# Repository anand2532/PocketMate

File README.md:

# PocketMate
A personal AI companion built on the Raspberry Pi CM5 (4GB; CM4 alternate). PocketMate helps you capture anything important, find it when you need it, and get the next step done: dependable, fast, privacy-conscious, and not a phone replacement.

MVP: push-to-talk voice assistant, local voice/typed notes, searchable memory with source-linked answers, camera OCR, reminders and action items, configurable local/cloud processing, and a physical mic mute. Hardware: 4.3" touchscreen, autofocus camera, dual MEMS mics, battery with USB-C charging, custom carrier PCB and a compact, serviceable enclosure (~125x75x20mm).

See [docs/PRD.md](docs/PRD.md) for the full product brief.

## Repository layout
- `hardware/kicad/` – schematics and carrier PCB (KiCad)
- `mechanical/freecad/` – enclosure CAD (FreeCAD)
- `software/` – Linux services, Qt/QML UI, firmware
- `docs/` – PRD and project documentation
- `research/` – notes, datasheets, experiments

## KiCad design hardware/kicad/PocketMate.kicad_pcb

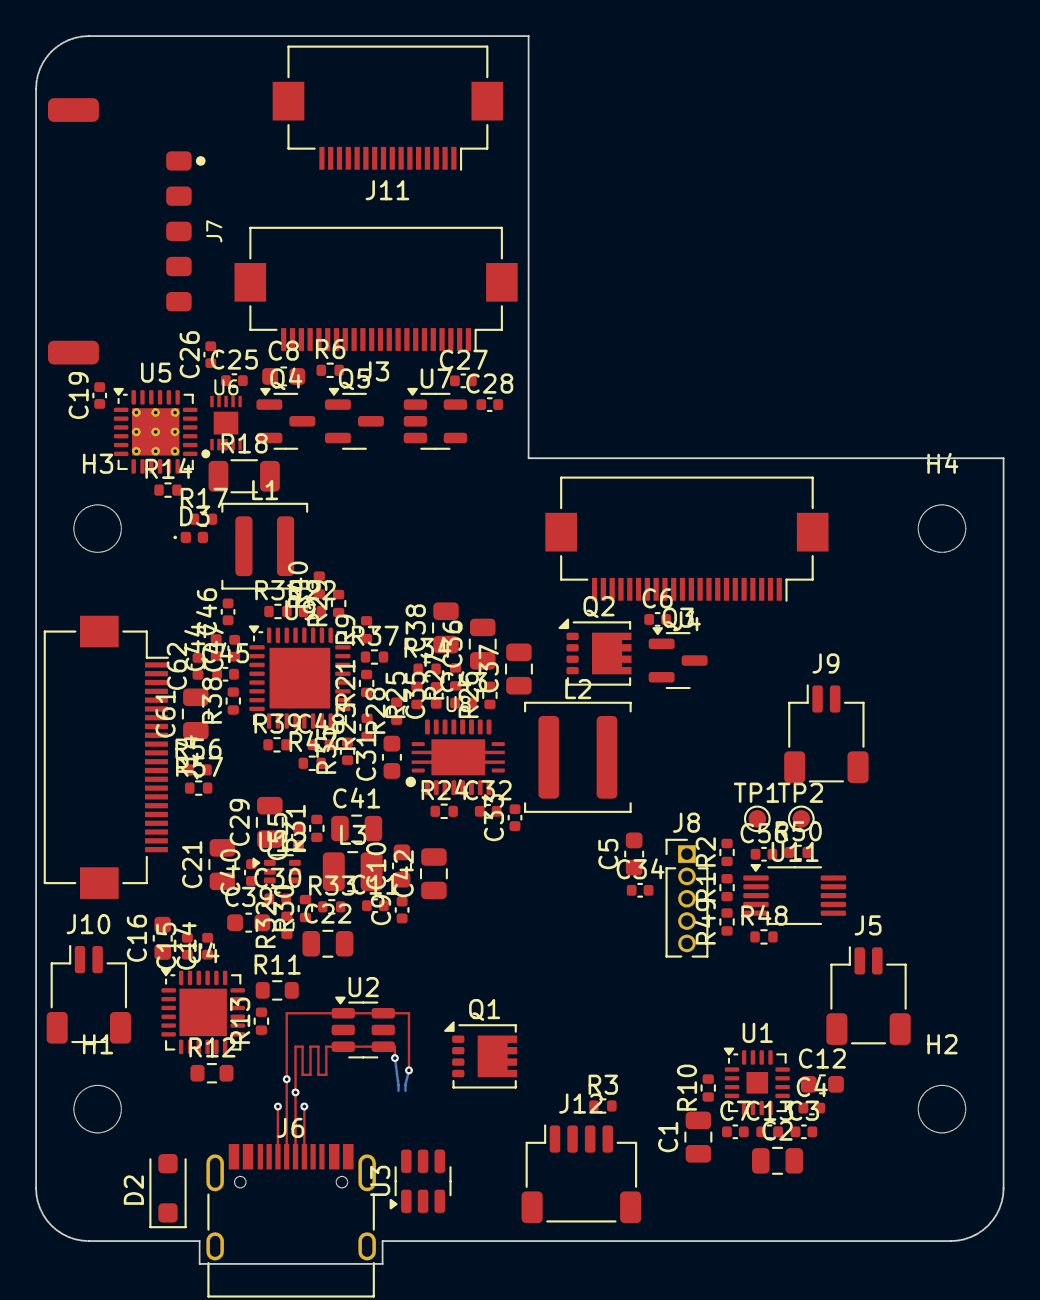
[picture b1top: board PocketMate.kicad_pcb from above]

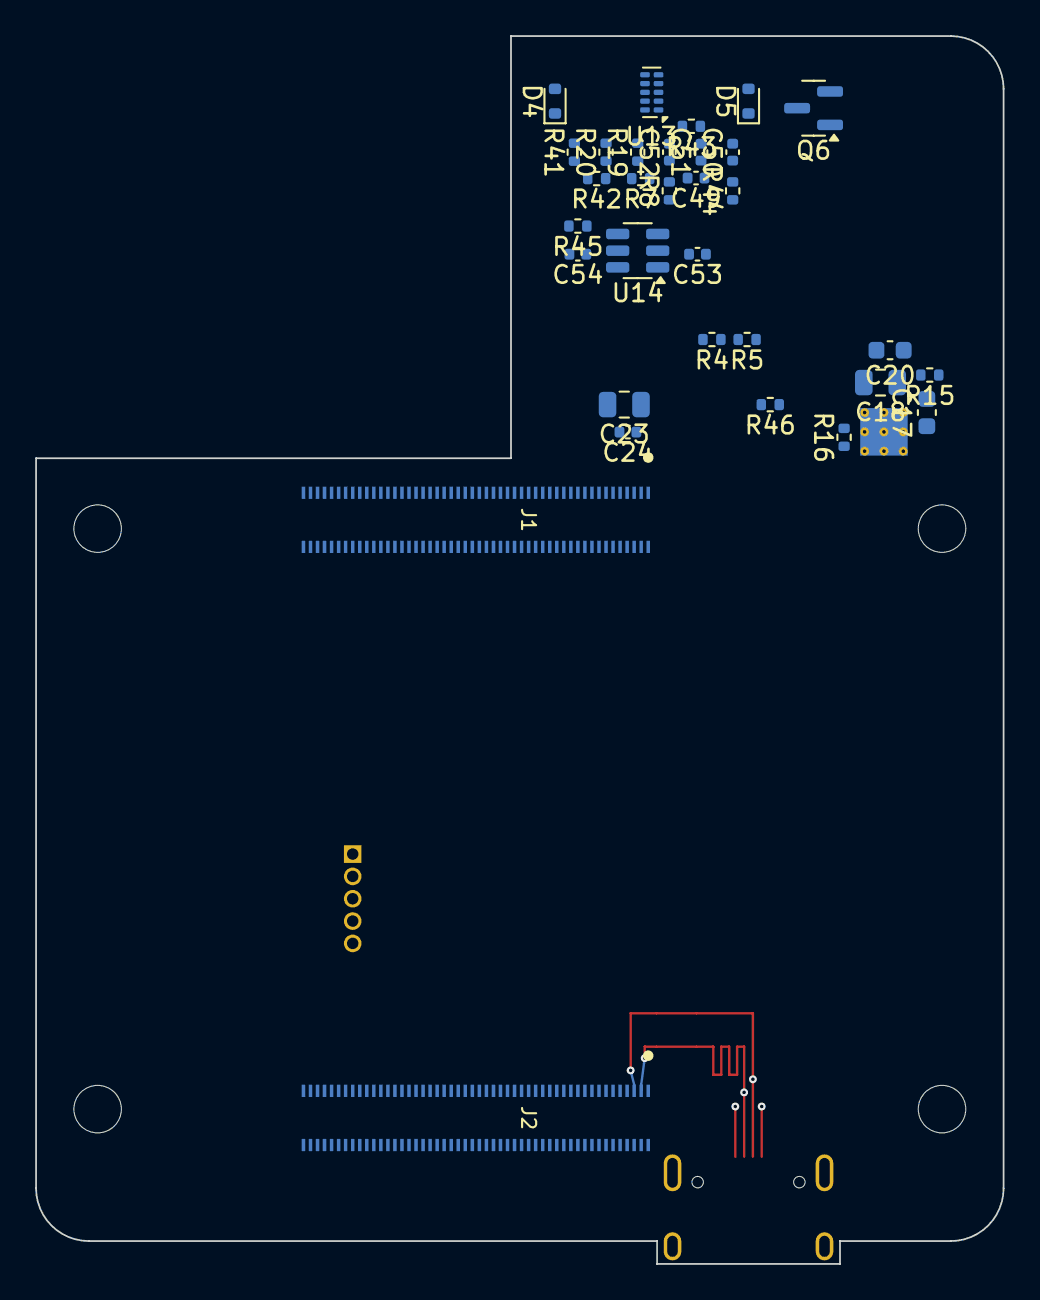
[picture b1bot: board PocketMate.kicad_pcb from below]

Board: 6 copper layers, 55.0 x 69.8 mm, 155 parts (32 on the bottom side), 130 nets.

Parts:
C1, C2, C21, C22, C29, C36, C37, C38, C41, C42, C61: 22uF; C_0805_2012Metric
C3, C4, C6, C9, C11, C13, C24, C28, C30, C32, C40, C44, C45, C47, C48, C53, C54, C62: 100nF; C_0402_1005Metric
C5, C8, C10, C12, C39: 10uF; C_0603_1608Metric
C7, C14, C15, C26, C27, C46, C55, C56: 1uF; C_0402_1005Metric
C16, C17: 1uF; C_0603_1608Metric
C18, C23: 10uF; C_0805_2012Metric
C19, C33: 47nF; C_0402_1005Metric
C20: 4.7uF; C_0603_1608Metric
C25: 470nF; C_0402_1005Metric
C31: 2.2uF; C_0603_1608Metric
C34: 2.7nF; C_0402_1005Metric
C35: 18pF; C_0402_1005Metric
C43, C49, C50, C51, C52: 10nF; C_0402_1005Metric
D2: SMF15A (VBUS TVS); D_SOD-123F
D3: GREEN charge; LED_0402_1005Metric
D4: RB521S30 (QON wake); D_SOD-523
D5: PESD5V0S1BB (ESD, MIC_SW_LIVE); D_SOD-523
H1, H2, H3, H4: MountingHole_2.7mm_M2.5
J1: 10164227-1001A1RLF; CM5_B2B_10164227_Pins1-100
J2: 10164227-1001A1RLF; CM5_B2B_10164227_Pins101-200
J3: DSI1 22p 0.5mm FH12-22S-0.5SH (Pi5 DSI pinout); Hirose_FH12-22S-0.5SH_1x22-1MP_P0.50mm_Horizontal
J4: CSI0 22p 0.5mm FH12-22S-0.5SH (Pi5 CSI pinout); Hirose_FH12-22S-0.5SH_1x22-1MP_P0.50mm_Horizontal
J5: Speaker 8R 1W; JST_SH_SM02B-SRSS-TB_1x02-1MP_P1.00mm_Horizontal
J6: TYPE-C-31-M-12; USB_C_Receptacle_HRO_TYPE-C-31-M-12
J7: Molex 205338-0005 (BAT+,BAT+,BAT-,BAT-,NTC); Molex_Pico-Lock_205338-0005_1x05-1MP_P2.00mm_Horizontal
J8: SWD (TC2030 pads); PinHeader_1x05_P1.27mm_Vertical
J9: LRA motor; JST_SH_SM02B-SRSS-TB_1x02-1MP_P1.00mm_Horizontal
J10: Skin NTC 10k B3435; JST_SH_SM02B-SRSS-TB_1x02-1MP_P1.00mm_Horizontal
J11: FH12-16S-0.5SH(55); Hirose_FH12-16S-0.5SH_1x16-1MP_P0.50mm_Horizontal
J12: Fan 5V/GND/PWM/TACH; JST_SH_SM04B-SRSS-TB_1x04-1MP_P1.00mm_Horizontal
J14: LTE link FH12-22S-0.5SH(55); Hirose_FH12-22S-0.5SH_1x22-1MP_P0.50mm_Horizontal
L1: 1uH XAL4020-102ME; L_Coilcraft_XAL4020-XXX
L2: 1uH XAL5030-102ME; L_Coilcraft_XAL5030-XXX
L3: 1uH DFE252012F-1R0M; L_1008_2520Metric
Q1, Q2: DMP3013SFV; Diodes_PowerDI3333-8
Q3, Q4, Q5, Q6: 2N7002; SOT-23
R1, R2, R4, R17, R49, R50: 2.2k; R_0402_1005Metric
R3, R9, R21, R22, R23, R28, R32, R36, R40: 10k; R_0402_1005Metric
R5, R6, R19, R20: 4.7k; R_0402_1005Metric
R7: 33R; R_0402_1005Metric
R8, R13, R29, R33, R34, R35, R41, R42, R43, R44, R46, R47, R48, R57: 100k; R_0402_1005Metric
R10: 1M; R_0402_1005Metric
R11: 1k; R_0603_1608Metric
R12: 220R; R_0603_1608Metric
R14: 130R 1%; R_0402_1005Metric
R15: 5.23k; R_0402_1005Metric
R16: 30.1k; R_0402_1005Metric
R18: 10m 1% 1206 0.5W; R_1206_3216Metric
R24: 150k 1%; R_0402_1005Metric
R25: 127k 1%; R_0402_1005Metric
R26: 182k 1%; R_0402_1005Metric
R27: 56k 1%; R_0402_1005Metric
R30: 100k 1%; R_0402_1005Metric
R31: 22.1k 1%; R_0402_1005Metric
R37: 10k 1%; R_0402_1005Metric
R38, R39: 1k; R_0402_1005Metric
R45, R56: 0R; R_0402_1005Metric
TP1: nRPIBOOT; TestPoint_Pad_D1.0mm
TP2: GND; TestPoint_Pad_D1.0mm
U1: MAX98357AETE+; TQFN-16-1EP_3x3mm_P0.5mm_EP1.23x1.23mm
U2: USBLC6-2SC6 (D+/D-); SOT-23-6
U3: USBLC6-2SC6 (CC1/CC2); SOT-23-6
U4: STUSB4500QTR; QFN-24-1EP_4x4mm_P0.5mm_EP2.7x2.7mm
U5: BQ25895RTWR; Texas_RTW_WQFN-24-1EP_4x4mm_P0.5mm_EP2.7x2.7mm_ThermalVias
U6: MAX17055ETB+; Maxim_TDFN-10-1EP_2x2.5mm_P0.4mm_EP1.4x1.3mm_MAX17055
U7: TPS7A0233PDBVR; SOT-23-5
U8: TPS61088RHLR; TI_RHL0020A_VQFN-20_3.5x4.5mm_TPS61088
U9: STM32U031K8U6; QFN-32-1EP_5x5mm_P0.5mm_EP3.45x3.45mm
U11: DRV2605LDGSR; VSSOP-10_3x3mm_P0.5mm
U12: TLV62585DRLR; SOT-563
U13: TPD4E05U06DQAR (flex buttons ESD); USON-10_2.5x1.0mm_P0.5mm
U14: TPS22917DBVR; SOT-23-6

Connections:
+3V3_AON: C27.1, C28.1, C44.1, C45.1, C46.1, J8.1, J11.2, R19.2, R20.2, R21.2, R22.2, R23.2, R41.2, R42.2, R43.2, R44.2, U2.5, U3.5, U7.5, U9.1, U9.5, U9.17
+3V3_PERIPH: C8.1, C9.1, C10.1, C11.1, C41.1, C42.1, J3.22, J4.22, J11.15, L3.2, R4.2, R30.1
+5V_CM5: C1.1, C2.1, C3.1, C4.1, C7.1, C12.1, C13.1, J1.77, J1.79, J1.81, J1.83, J1.85, J1.87, J12.1, Q2.5, R56.1, U1.7, U1.8
/Audio/SPK_N: J5.2, U1.10
/Audio/SPK_P: J5.1, U1.9
/CM5/CM5_1V8: J1.88, J1.90
/CM5/CM5_NRPIBOOT: J1.93, TP1.1
/CM5/FAN_PWM: J1.19, J12.3
/CM5/FAN_TACH: J1.16, J12.4, R3.1
/DisplayCamera/DSI_PIN17: J3.17, R4.1
/LTE/LTE_USB_VBUS: J14.13, R56.2
/MCU/CM5_PMIC_OFF_DRV: Q5.1, R47.1, U9.13
/MCU/CM5_PWRBTN_DRV: Q4.1, R46.1, U9.12
/MCU/MCU_BOOT0: R36.1, U9.31
/MCU/MCU_NRST: C47.1, J8.4, U9.4
/MCU/MCU_RX: R39.1, U9.9
/MCU/MCU_TX: R38.1, U9.8
/MCU/MICSW_QOD: R45.1, U14.5
/MCU/MIC_PWR_EN: U9.21, U14.3
/MCU/NTC_ADC: C48.1, J10.1, R37.2, U9.14
/MCU/NTC_BIAS: R37.1, U9.22
/MCU/SWCLK: J8.3, U9.24
/MCU/SWDIO: J8.2, U9.23
/PowerInput/BAT_N: C24.2, C25.2, J7.3, J7.4, R18.1, U6.2, U6.6, U6.11
/PowerInput/BQ_QON_N: D4.2, U5.12
/PowerInput/CHG_BTST: C19.1, U5.21
/PowerInput/CHG_ILIM: R14.1, U5.10
/PowerInput/CHG_PMID: C18.1, U5.23
/PowerInput/CHG_REGN: C20.1, R15.1, R17.1, U5.22
/PowerInput/CHG_STAT: D3.1, U5.4
/PowerInput/CHG_STAT_LED_A: D3.2, R17.2
/PowerInput/CHG_SW: C19.2, L1.1, U5.19, U5.20
/PowerInput/CHG_TS: J7.5, R15.2, R16.1, U5.11
/PowerInput/GAUGE_REG: C25.1, U6.7
/PowerInput/PD_DISCH: R12.1, U4.9
/PowerInput/PD_VBUS_VS: R11.1, U4.18
/PowerInput/PD_VREG_1V2: C14.1, U4.21
/PowerInput/PD_VREG_2V7: C15.1, U4.23
/PowerInput/USB_CC1: J6.A5, U3.1, U3.6, U4.1, U4.2
/PowerInput/USB_CC2: J6.B5, U3.3, U3.4, U4.4, U4.5
/PowerInput/VBUS_C: C16.1, D2.2, J6.A4, J6.A9, J6.B4, J6.B9, Q1.1, Q1.2, Q1.3, R11.2, R13.2, U4.24
/PowerInput/VBUS_CHG: C17.1, Q1.5, R12.2, U5.1
/PowerInput/VBUS_EN_SNK: Q1.4, R13.1, U4.16
/Regulators/+5V_BOOST: C36.1, C37.1, C38.1, C43.2, Q2.1, Q2.2, Q2.3, R26.1, R34.2, U8.14, U8.15, U8.16
/Regulators/BST_BOOT: C32.1, U8.8
/Regulators/BST_COMP: C35.1, R28.1, U8.18
/Regulators/BST_COMP_RC: C34.1, R28.2
/Regulators/BST_FB: R26.2, R27.1, U8.17
/Regulators/BST_FSW: R24.1, U8.3
/Regulators/BST_ILIM: R25.1, U8.19
/Regulators/BST_SS: C33.1, U8.10
/Regulators/BST_SW: C32.2, L2.2, R24.2, U8.4, U8.5, U8.6, U8.7
/Regulators/BST_VCC: C31.1, U8.1
/Regulators/BUCK3V3_EN: R32.2, R33.1, U12.4
/Regulators/BUCK3V3_FB: R30.2, R31.1, U12.5
/Regulators/BUCK3V3_SW: L3.1, U12.2
/Regulators/LSW_GATE: C43.1, Q2.4, Q3.3, R34.1
/Sensors/HAPTIC_REG: C56.1, U11.1
/Sensors/LRA_N: J9.2, U11.9
/Sensors/LRA_P: J9.1, U11.7
AMP_SD_MODE: J1.48, R10.1, U1.4
BOOST_EN: R29.1, U8.2, U9.25
BTN_ACTION_N: C50.1, J11.16, R42.1, U9.7, U13.2
BTN_PWR_N: C49.1, D4.1, J11.12, R41.1, U9.6, U13.1
BTN_VOLDN_N: C52.1, J11.14, R44.1, U9.11, U13.5
BTN_VOLUP_N: C51.1, J11.13, R43.1, U9.10, U13.4
CAM_GPIO0: J1.97, J4.17
CAM_GPIO1: J1.100, J4.18
CAM_I2C_SCL: J1.80, J4.20
CAM_I2C_SDA: J1.82, J4.21
CHG_INT_N: R22.1, U5.7, U9.28
CM5_3V3: C5.1, C6.1, J1.78, J1.84, J1.86, R1.2, R2.2, R3.2, R5.2, R6.2, R9.2, R32.1, R40.2, R49.2, R50.2
CM5_5V_EN: Q3.1, R35.1, U9.15
CM5_ALIVE: J1.47, U9.27
CM5_PMIC_EN: J1.99, Q5.3
CM5_PWR_BUTTON: J1.92, Q4.3
CSI_C_N: J2.127, J4.8
CSI_C_P: J2.129, J4.9
CSI_D0_N: J2.115, J4.2
CSI_D0_P: J2.117, J4.3
CSI_D1_N: J2.121, J4.5
CSI_D1_P: J2.123, J4.6
CSI_D2_N: J2.133, J4.11
CSI_D2_P: J2.135, J4.12
CSI_D3_N: J2.139, J4.14
CSI_D3_P: J2.141, J4.15
DSI_C_N: J2.187, J3.8
DSI_C_P: J2.189, J3.9
DSI_D0_N: J2.175, J3.2
DSI_D0_P: J2.177, J3.3
DSI_D1_N: J2.181, J3.5
DSI_D1_P: J2.183, J3.6
DSI_D2_N: J2.193, J3.11
DSI_D2_P: J2.195, J3.12
DSI_D3_N: J2.194, J3.14
DSI_D3_P: J2.196, J3.15
DSI_I2C_SCL: J1.35, J3.20, R6.1
DSI_I2C_SDA: J1.36, J3.21, R5.1
GAUGE_ALRT_N: R23.1, U6.8, U9.18
GND: C1.2, C2.2, C3.2, C4.2, C5.2, C6.2, C7.2, C8.2, C9.2, C10.2, C11.2, C12.2, C13.2, C14.2, C15.2, C16.2, C17.2, C18.2, C20.2, C21.2, C22.2, C23.2, C26.2, C27.2, C28.2, C29.2, C30.2, C31.2, C33.2, C34.2, C35.2, C36.2, C37.2, C38.2, C39.2, C40.2, C41.2, C42.2, C44.2, C45.2, C46.2, C47.2, C48.2, C49.2, C50.2, C51.2, C52.2, C53.2, C54.2, C55.2, C56.2, C61.2, C62.2, D2.1, D5.1, J1.1, J1.2, J1.7, J1.8, J1.13, J1.14, J1.22, J1.23, J1.32, J1.33, J1.42, J1.43, J1.52, J1.53, J1.59, J1.60, J1.65, J1.66, J1.71, J1.74, J1.98, J2.107, J2.108, J2.113, J2.114, J2.119, J2.120, J2.125, J2.126, J2.131, J2.132, J2.137, J2.138, J2.144, J2.150, J2.155, J2.156, J2.161, J2.162, J2.167, J2.168, J2.173, J2.174, J2.179, J2.180, J2.185, J2.186, J2.191, J2.192, J2.197, J2.198, J3.1, J3.4, J3.7, J3.10, J3.13, J3.16, J3.19, J4.1, J4.4, J4.7, J4.10, J4.13, J4.16, J4.19, J6.A1, J6.A12, J6.B1, J6.B12, J6.S1, J8.5, J10.2, J11.1, J11.5, J11.8, J12.2, J14.7, J14.8, J14.9, J14.12, J14.14, J14.22, Q3.2, Q4.2, Q5.2, Q6.2, R8.2, R10.2, R14.2, R16.2, R18.2, R25.2, R27.2, R29.2, R31.2, R33.2, R35.2, R36.2, R46.2, R47.2, R48.2, R57.2, TP2.1, U1.3, U1.11, U1.15, U1.17, U2.2, U3.2, U4.6, U4.10, U4.12, U4.13, U4.22, U4.25, U5.8, U5.9, U5.17, U5.18, U5.25, U6.5, U7.2, U8.11, U8.12, U8.20, U8.21, U9.16, U9.32, U9.33, U11.4, U11.8, U12.1, U13.3, U13.8, U14.2
HAPTIC_EN: J1.46, R48.1, U11.5
I2C1_SCL: J1.56, R2.1, R50.1, U11.2
I2C1_SDA: J1.58, R1.1, R49.1, U11.3
I2S_BCLK: J1.49, J11.4, U1.16
I2S_DIN: J1.27, R7.2
I2S_DOUT: J1.25, U1.1
I2S_LRCLK: J1.26, J11.6, U1.14
LTE_AP_READY: J1.41, J14.21
LTE_PWRKEY: J1.30, J14.16
LTE_PWR_EN: J1.34, J14.15, R57.1
LTE_RESET: J1.28, J14.17
LTE_RI: J1.31, J14.20
LTE_STATUS: J1.29, J14.19
LTE_USB_DM: J2.136, J14.10
LTE_USB_DP: J2.134, J14.11
LTE_W_DISABLE_N: J1.24, J14.18
MCU_I2C_SCL: J11.10, R20.1, U4.7, U5.5, U6.3, U9.29
MCU_I2C_SDA: J11.9, R19.1, U4.8, U5.6, U6.4, U9.30
MCU_IRQ_N: J1.54, R40.1, U9.26
MIC_DATA_GATED: J11.7, R7.1
MIC_FEED: C54.1, J11.3, R45.2, U14.6
MIC_SW_LIVE: C53.1, D5.2, J11.11, Q6.1, R8.1, U14.1
MUTE_STATUS_IO: J1.50, Q6.3, R9.1, U9.20
PD_ALERT_N: R21.1, U4.19, U9.19
UART0_RX: J1.51, R38.2
UART0_TX: J1.55, R39.2
USB_DM: J2.103, J6.A7, J6.B7, U2.3, U2.4
USB_DP: J2.105, J6.A6, J6.B6, U2.1, U2.6
VBAT: C23.1, C24.1, C26.1, J7.1, J7.2, U5.13, U5.14, U6.10, U7.1, U7.3
VSYS: C21.1, C22.1, C29.1, C30.1, C39.1, C40.1, C55.1, C61.1, C62.1, J14.1, J14.2, J14.3, J14.4, J14.5, J14.6, L1.2, L2.1, U5.15, U5.16, U8.9, U11.6, U11.10, U12.3

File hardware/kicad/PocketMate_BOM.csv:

"Reference","Value","Footprint","QUANTITY","DNP"
"C1,C2,C21,C22,C29,C36,C37,C38,C41,C42","22uF","Capacitor_SMD:C_0805_2012Metric","10",""
"C3,C4,C6,C9,C11,C13,C24,C28,C30,C32,C40,C44,C45,C47,C48,C53,C54,C57,C58,C59","100nF","Capacitor_SMD:C_0402_1005Metric","20",""
"C5,C8,C10,C12,C39","10uF","Capacitor_SMD:C_0603_1608Metric","5",""
"C7,C14,C15,C26,C27,C46,C55,C56,C60","1uF","Capacitor_SMD:C_0402_1005Metric","9","DNP"
"C16,C17","1uF","Capacitor_SMD:C_0603_1608Metric","2",""
"C18,C23","10uF","Capacitor_SMD:C_0805_2012Metric","2",""
"C19,C33","47nF","Capacitor_SMD:C_0402_1005Metric","2",""
"C20","4.7uF","Capacitor_SMD:C_0603_1608Metric","1",""
"C25","470nF","Capacitor_SMD:C_0402_1005Metric","1",""
"C31","2.2uF","Capacitor_SMD:C_0603_1608Metric","1",""
"C34","2.7nF","Capacitor_SMD:C_0402_1005Metric","1",""
"C35","18pF","Capacitor_SMD:C_0402_1005Metric","1",""
"C43,C49,C50,C51,C52","10nF","Capacitor_SMD:C_0402_1005Metric","5",""
"D1","RED mic-muted","LED_SMD:LED_0402_1005Metric","1",""
"D2","SMF15A (VBUS TVS)","Diode_SMD:D_SOD-123F","1",""
"D3","GREEN charge","LED_SMD:LED_0402_1005Metric","1",""
"D4","RB521S30 (QON wake)","Diode_SMD:D_SOD-523","1",""
"D5","PESD5V0S1BB (ESD, MIC_SW_LIVE)","Diode_SMD:D_SOD-523","1",""
"D6","GREEN REC (APTD1608LZGCK)","LED_SMD:LED_0603_1608Metric","1",""
"J1","10164227-1001A1RLF","PocketMate:CM5_B2B_10164227_Pins1-100","1",""
"J2","10164227-1001A1RLF","PocketMate:CM5_B2B_10164227_Pins101-200","1",""
"J3","DSI1 22p 0.5mm FH12-22S-0.5SH (Pi5 DSI pinout)","Connector_FFC-FPC:Hirose_FH12-22S-0.5SH_1x22-1MP_P0.50mm_Horizontal","1",""
"J4","CSI0 22p 0.5mm FH12-22S-0.5SH (Pi5 CSI pinout)","Connector_FFC-FPC:Hirose_FH12-22S-0.5SH_1x22-1MP_P0.50mm_Horizontal","1",""
"J5","Speaker 8R 1W","Connector_JST:JST_SH_SM02B-SRSS-TB_1x02-1MP_P1.00mm_Horizontal","1",""
"J6","TYPE-C-31-M-12","Connector_USB:USB_C_Receptacle_HRO_TYPE-C-31-M-12","1",""
"J7","Molex 205338-0005 (BAT+,BAT+,BAT-,BAT-,NTC)","PocketMate:Molex_Pico-Lock_205338-0005_1x05-1MP_P2.00mm_Horizontal","1",""
"J8","SWD (TC2030 pads)","Connector_PinHeader_1.27mm:PinHeader_1x05_P1.27mm_Vertical","1",""
"J9","LRA motor","Connector_JST:JST_SH_SM02B-SRSS-TB_1x02-1MP_P1.00mm_Horizontal","1","DNP"
"J10","Skin NTC 10k B3435","Connector_JST:JST_SH_SM02B-SRSS-TB_1x02-1MP_P1.00mm_Horizontal","1",""
"J11","FH12-16S-0.5SH(55)","Connector_FFC-FPC:Hirose_FH12-16S-0.5SH_1x16-1MP_P0.50mm_Horizontal","1",""
"J12","Fan 5V/GND/PWM/TACH","Connector_JST:JST_SH_SM04B-SRSS-TB_1x04-1MP_P1.00mm_Horizontal","1","DNP"
"J13","Flex tail to carrier J11 (placeholder)","PocketMate:FlexTail_16P_P0.50mm","1",""
"L1","1uH XAL4020-102ME","Inductor_SMD:L_Coilcraft_XAL4020-XXX","1",""
"L2","1uH XAL5030-102ME","Inductor_SMD:L_Coilcraft_XAL5030-XXX","1",""
"L3","1uH DFE252012F-1R0M","Inductor_SMD:L_1008_2520Metric","1",""
"MK1","SPH0645LM4H-B (Left, SEL=GND)","Sensor_Audio:Knowles_SPH0645LM4H-6_3.5x2.65mm","1",""
"MK2","SPH0645LM4H-B (Right, SEL=VDD)","Sensor_Audio:Knowles_SPH0645LM4H-6_3.5x2.65mm","1",""
"Q1,Q2","DMP3013SFV","Package_SON:Diodes_PowerDI3333-8","2",""
"Q3,Q4,Q5,Q6","2N7002","Package_TO_SOT_SMD:SOT-23","4",""
"R1,R2,R4,R17,R49,R50","2.2k","Resistor_SMD:R_0402_1005Metric","6","DNP"
"R3,R9,R21,R22,R23,R28,R32,R36,R40","10k","Resistor_SMD:R_0402_1005Metric","9","DNP"
"R5,R6,R19,R20","4.7k","Resistor_SMD:R_0402_1005Metric","4",""
"R7","33R","Resistor_SMD:R_0402_1005Metric","1",""
"R8,R13,R29,R33,R34,R35,R41,R42,R43,R44,R46,R47,R48,R53","100k","Resistor_SMD:R_0402_1005Metric","14","DNP"
"R10","1M","Resistor_SMD:R_0402_1005Metric","1",""
"R11","1k","Resistor_SMD:R_0603_1608Metric","1",""
"R12","220R","Resistor_SMD:R_0603_1608Metric","1",""
"R14","130R 1%","Resistor_SMD:R_0402_1005Metric","1",""
"R15","5.23k","Resistor_SMD:R_0402_1005Metric","1",""
"R16","30.1k","Resistor_SMD:R_0402_1005Metric","1",""
"R18","10m 1% 1206 0.5W","Resistor_SMD:R_1206_3216Metric","1",""
"R24","150k 1%","Resistor_SMD:R_0402_1005Metric","1",""
"R25","127k 1%","Resistor_SMD:R_0402_1005Metric","1",""
"R26","182k 1%","Resistor_SMD:R_0402_1005Metric","1",""
"R27","56k 1%","Resistor_SMD:R_0402_1005Metric","1",""
"R30","100k 1%","Resistor_SMD:R_0402_1005Metric","1",""
"R31","22.1k 1%","Resistor_SMD:R_0402_1005Metric","1",""
"R37","10k 1%","Resistor_SMD:R_0402_1005Metric","1",""
"R38,R39,R54","1k","Resistor_SMD:R_0402_1005Metric","3",""
"R45,R51,R52","0R","Resistor_SMD:R_0402_1005Metric","3",""
"R55","1.3k","Resistor_SMD:R_0402_1005Metric","1",""
"SW1","POWER","Button_Switch_SMD:SW_SPST_PTS810","1",""
"SW2","ACTION","Button_Switch_SMD:SW_SPST_PTS810","1",""
"SW3","VOL+","Button_Switch_SMD:SW_SPST_PTS810","1",""
"SW4","VOL-","Button_Switch_SMD:SW_SPST_PTS810","1",""
"SW5","MIC MUTE (DPDT slide)","Button_Switch_SMD:SW_DPDT_CK_JS202011JCQN","1",""
"TP1","nRPIBOOT","TestPoint:TestPoint_Pad_D1.0mm","1",""
"TP2","GND","TestPoint:TestPoint_Pad_D1.0mm","1",""
"U1","MAX98357AETE+","Package_DFN_QFN:TQFN-16-1EP_3x3mm_P0.5mm_EP1.23x1.23mm","1",""
"U2","USBLC6-2SC6 (D+/D-)","Package_TO_SOT_SMD:SOT-23-6","1",""
"U3","USBLC6-2SC6 (CC1/CC2)","Package_TO_SOT_SMD:SOT-23-6","1",""
"U4","STUSB4500QTR","Package_DFN_QFN:QFN-24-1EP_4x4mm_P0.5mm_EP2.7x2.7mm","1",""
"U5","BQ25895RTWR","Package_DFN_QFN:Texas_RTW_WQFN-24-1EP_4x4mm_P0.5mm_EP2.7x2.7mm_ThermalVias","1",""
"U6","MAX17055ETB+","PocketMate:Maxim_TDFN-10-1EP_2x2.5mm_P0.4mm_EP1.4x1.3mm_MAX17055","1",""
"U7","TPS7A0233PDBVR","Package_TO_SOT_SMD:SOT-23-5","1",""
"U8","TPS61088RHLR","PocketMate:TI_RHL0020A_VQFN-20_3.5x4.5mm_TPS61088","1",""
"U9","STM32U031K8U6","Package_DFN_QFN:QFN-32-1EP_5x5mm_P0.5mm_EP3.45x3.45mm","1",""
"U10","VEML7700-TT","PocketMate:Vishay_VEML7700","1",""
"U11","DRV2605LDGSR","Package_SO:VSSOP-10_3x3mm_P0.5mm","1","DNP"
"U12","TLV62585DRLR","Package_TO_SOT_SMD:SOT-563","1",""
"U13","TPD4E05U06DQAR (flex buttons ESD)","Package_SON:USON-10_2.5x1.0mm_P0.5mm","1",""
"U14","TPS22917DBVR","Package_TO_SOT_SMD:SOT-23-6","1",""
